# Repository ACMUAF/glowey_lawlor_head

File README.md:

The code folder contains the Arduino libraries used in the glowing eyes code (neopixel).
The code folder also has the default firmware for the glowing eyes code (glow.ino).

To flash an ATTINY85, follow this guide:
	http://highlowtech.org/?p=1695

The two eagle files for the board are in the eagle folder.

The Lawlor head stl is included as well in the stl folder.
The Lawlor head stl was printed with no support, 0% fill, no floor, 1 shell (probably be better with 2 shells).

The flyer is included...just because...

Links to parts (note, these are not 1x):
	http://www.ebay.com/itm/300954972934		pcbs
	http://www.ebay.com/itm/201410141836		8pin socket
	http://www.ebay.com/itm/261987455019		attiny85
	http://www.ebay.com/itm/261819895437		5v reg
	http://www.ebay.com/itm/151492714462		9v connectors
	http://www.ebay.com/itm/140942027356		tact switches
	http://www.ebay.com/itm/331590500783		switches
	http://www.ebay.com/itm/251889773335		8pin usb thingy
	http://www.ebay.com/itm/111164910188		ws2812 leds

Other Links (other cool stuff we talked about):
	http://www.ebay.com/itm/130999706774		mill
	http://www.ebay.com/itm/300954972934		laser cutter
	http://www.ebay.com/itm/201214891226		3d printer

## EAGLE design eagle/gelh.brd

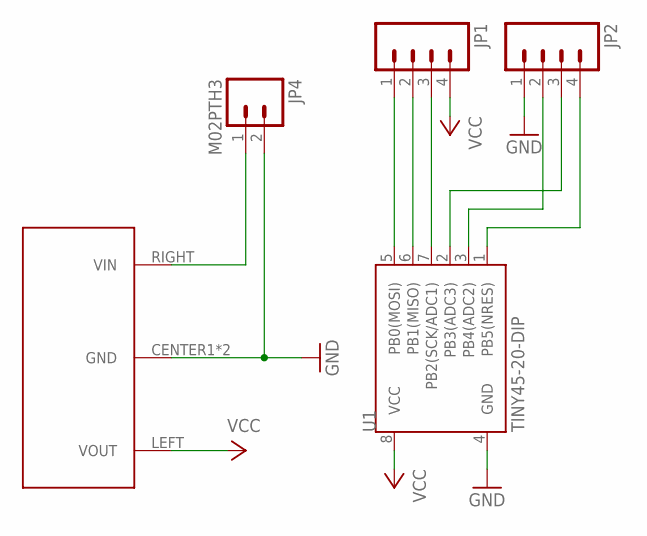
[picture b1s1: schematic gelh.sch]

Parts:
JP1, JP2: M04LONGPADS; 1X04_LONGPADS
JP4: M02PTH3; 1X02_LONGPADS
U1: TINY45-20-DIP; DIP08
U$1: 78L05; SOT89

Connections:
GND: JP2.1, JP4.2, U1.4 (GND), U$1.CENTER1 (GND), U$1.CENTER2 (GND)
unnamed: JP4.1, U$1.RIGHT (VIN)
unnamed: JP1.1, U1.5 (PB0(MOSI))
unnamed: JP1.2, U1.6 (PB1(MISO))
unnamed: JP2.4, U1.1 (PB5(NRES))
unnamed: JP2.3, U1.2 (PB3(ADC3))
unnamed: JP2.2, U1.3 (PB4(ADC2))
unnamed: JP1.3, U1.7 (PB2(SCK/ADC1))
VCC: JP1.4, U1.8 (VCC), U$1.LEFT (VOUT)

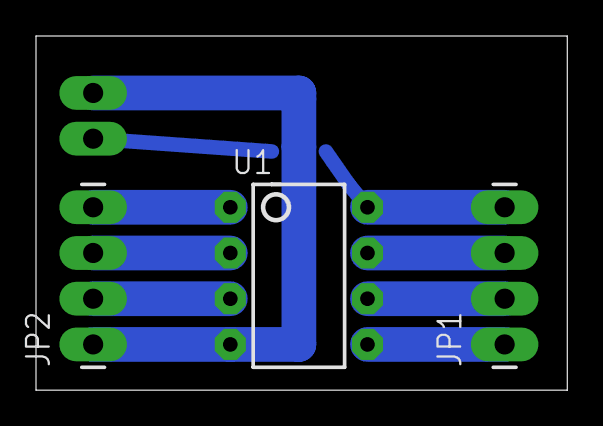
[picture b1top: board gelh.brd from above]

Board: 2 copper layers, 29.5 x 19.7 mm, 5 parts (1 on the bottom side), 9 nets.

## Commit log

2015-10-08 Added files.
2015-10-08 Added a picture for clarity...
2015-10-11 Wrong read pin...

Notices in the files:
parts and their libraries:
SparkFun-DigitalIC: Licensing: CC v3.0 Share-Alike You are welcome to use this library for commercial purposes.
